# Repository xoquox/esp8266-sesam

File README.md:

# esp8266-sesam

Universal Wifi door opener. 

A project by [schinken](https://github.com/schinken "schinkens Github") and [xoquox](https://github.com/xoquox "xoquoxs Github")

# Hardware

Our hardware works with a ESP-08 or ESP-12e modul. It uses nice little DIL relays, becaus we can direct control them with TTL-signals. What I think is very nice for a relay. 

# Webinterface
  TODO

# REST-API
  TODO

# License
  TODOh

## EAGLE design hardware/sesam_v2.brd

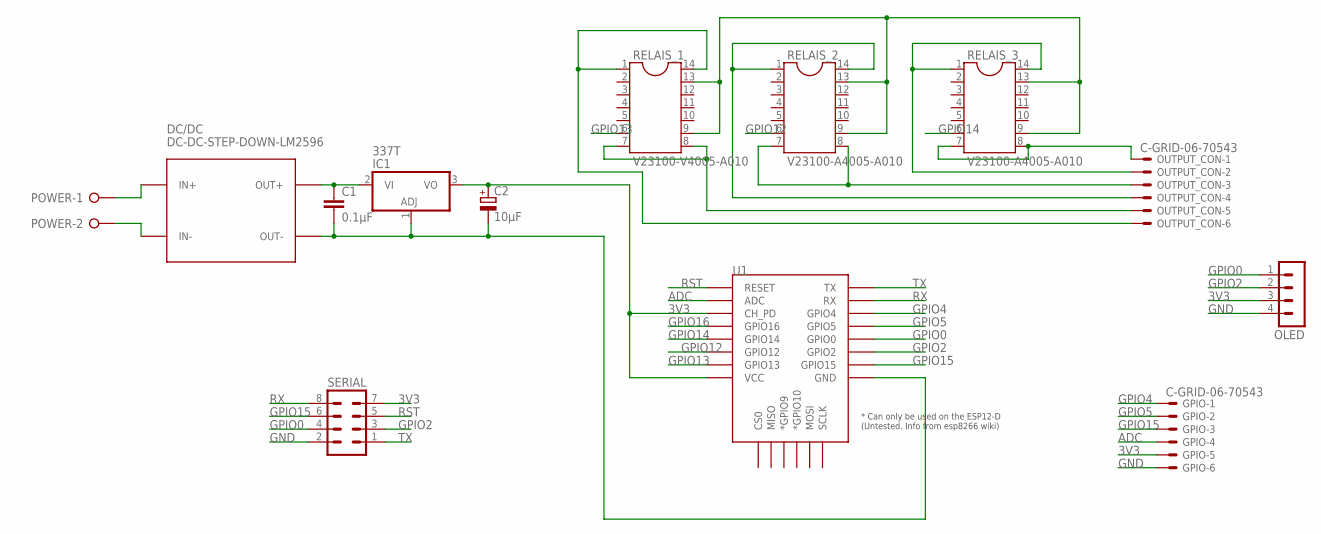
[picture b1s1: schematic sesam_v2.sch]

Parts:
C1: 0.1µF; C0805
C2: 10µF; E2-5
DC/DC: DC-DC-STEP-DOWN-LM2596
GPIO: C-GRID-06-70543; 70543-06
IC1: 337T; TO220H
OLED: MA04-1
OUTPUT_CON: C-GRID-06-70543; 70543-06
POWER: W237-02P; W237-132
RELAIS_1: V23100-V4005-A010; SOCKET-14
RELAIS_2, RELAIS_3: V23100-A4005-A010; SOCKET-14
SERIAL: MA04-2
U1: ESP12ESMD; ESP12E-SMD

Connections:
3V3: C2.+, GPIO.5, IC1.3 (VO), OLED.3, SERIAL.7, U1.CH_PD, U1.VCC
ADC: GPIO.4, U1.ADC
GND: C1.2, C2.-, DC/DC.IN-, DC/DC.OUT-, GPIO.6, IC1.1 (ADJ), OLED.4, POWER.2, RELAIS_1.9, RELAIS_1.13, RELAIS_2.9, RELAIS_2.13, RELAIS_3.9, RELAIS_3.13, SERIAL.2, U1.GND
GPIO0: OLED.1, SERIAL.4, U1.GPIO0
GPIO2: OLED.2, SERIAL.3, U1.GPIO2
GPIO4: GPIO.1, U1.GPIO4
GPIO5: GPIO.2, U1.GPIO5
GPIO12: RELAIS_2.6, U1.GPIO12
GPIO13: RELAIS_1.6, U1.GPIO13
GPIO14: RELAIS_3.6, U1.GPIO14
GPIO15: GPIO.3, SERIAL.6, U1.GPIO15
GPIO16: U1.GPIO16
unnamed 14: OUTPUT_CON.2, RELAIS_3.1, RELAIS_3.14; also elsewhere on the board
unnamed: DC/DC.IN+, POWER.1
unnamed 16: OUTPUT_CON.1, RELAIS_3.7, RELAIS_3.8; also elsewhere on the board
unnamed 17: OUTPUT_CON.4, RELAIS_2.1, RELAIS_2.14; also elsewhere on the board
unnamed 18: OUTPUT_CON.3, RELAIS_2.7, RELAIS_2.8; also elsewhere on the board
unnamed 19: OUTPUT_CON.6, RELAIS_1.1, RELAIS_1.14; also elsewhere on the board
unnamed 20: OUTPUT_CON.5, RELAIS_1.7, RELAIS_1.8; also elsewhere on the board
POWER: C1.1, DC/DC.OUT+, IC1.2 (VI)
RST: SERIAL.5, U1.RESET
RX: SERIAL.8, U1.RXD0 (RX)
TX: SERIAL.1, U1.TXD0 (TX)

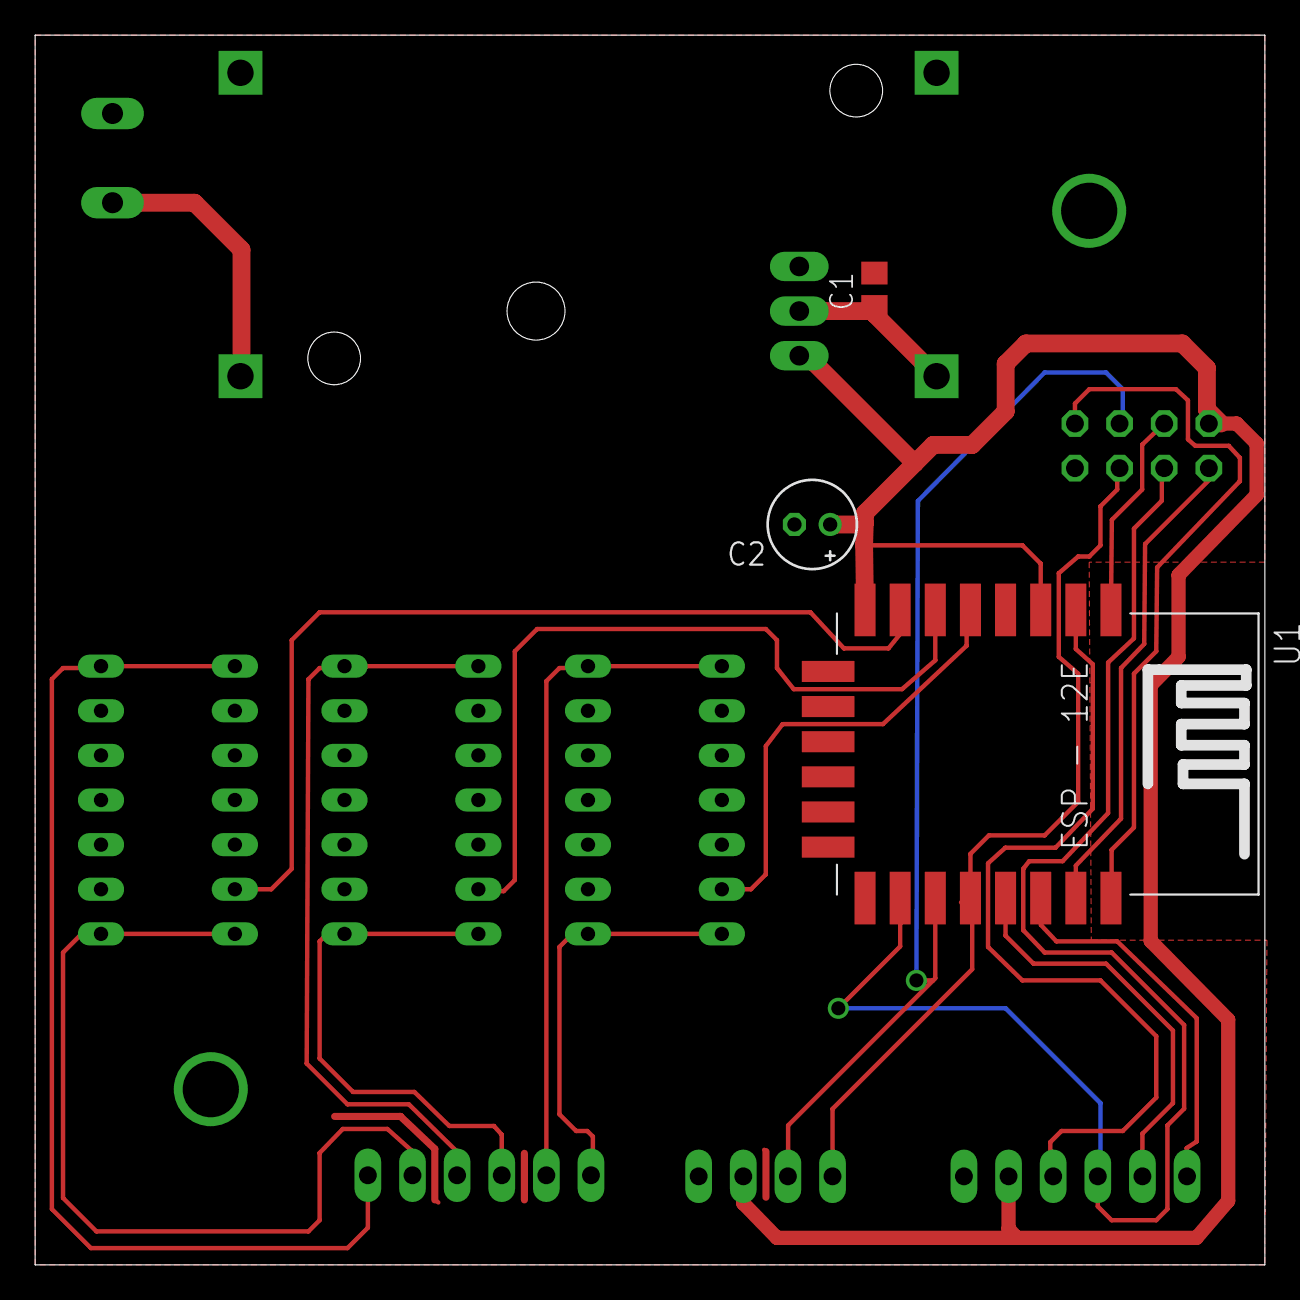
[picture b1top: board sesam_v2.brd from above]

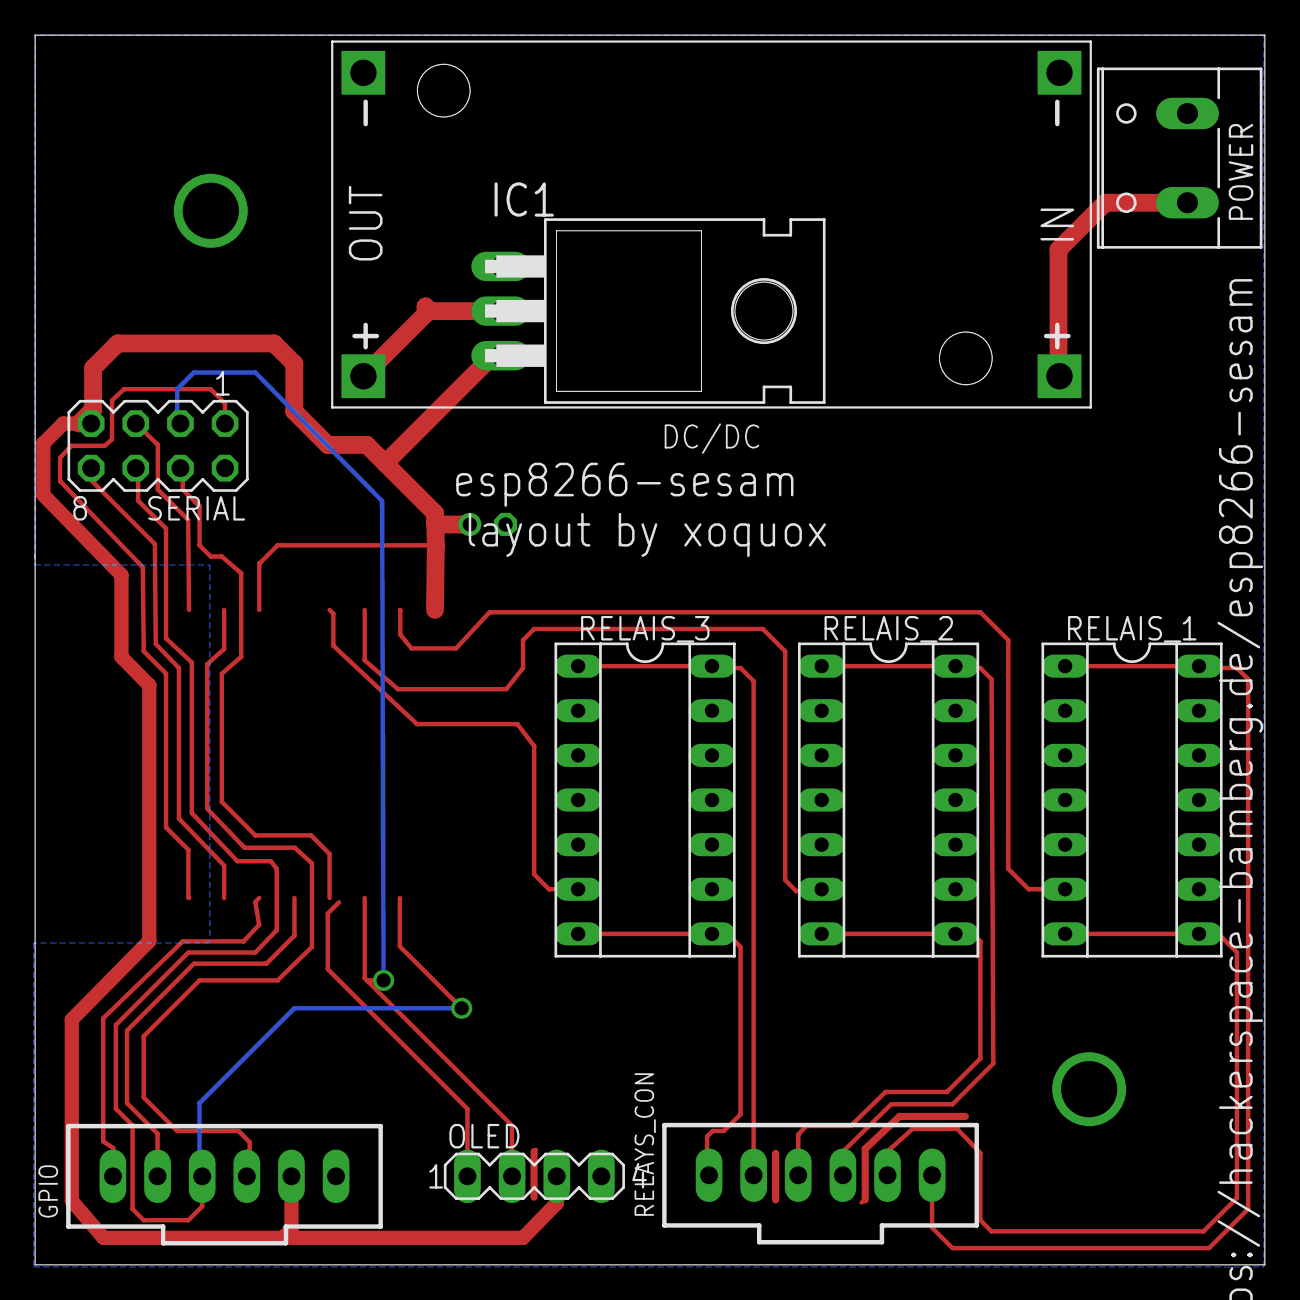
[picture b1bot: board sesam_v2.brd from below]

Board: 2 copper layers, 70.0 x 70.0 mm, 13 parts (10 on the bottom side), 22 nets.

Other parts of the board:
RELAYS_CON: C-GRID-06-70543; 70543-06

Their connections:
unnamed 14: RELAYS_CON.2; also elsewhere on the board
unnamed 16: RELAYS_CON.1; also elsewhere on the board
unnamed 17: RELAYS_CON.4; also elsewhere on the board
unnamed 18: RELAYS_CON.3; also elsewhere on the board
unnamed 19: RELAYS_CON.6; also elsewhere on the board
unnamed 20: RELAYS_CON.5; also elsewhere on the board

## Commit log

2016-02-12 Set pinmode; Add caching directives
2016-02-12 Add random parameter to prevent browser caching
2016-02-12 Prevent caching also on /
2016-02-12 Introduce open.html to avoid caching
2016-05-16 hardware files added
2016-05-18 new layout by hallojoh
2016-05-18 Create a Readme.
2016-05-18 new layout, all non smd components mirrored
2016-05-18 Bottom added
2016-05-18 layout images added
2016-05-19 minor changes
2016-05-19 little changes
2016-05-19 new nice layout
2016-05-19 ready for first board
2016-05-19 some little changes, .gitignore for usless eagle files added and also some of this files removed from tree
2016-05-20 removed eagle backup files from tree
2016-05-20 minor tweeks
2016-05-21 rename of source file
2016-05-21 nice new layout and board, better power supply added
2016-05-21 fixed power regulator
2016-05-22 some layout tweeks
2016-05-22 fixed GND connections
2016-05-22 Make button/relais configurable
2016-05-22 Fix whitespaces and indention
2016-05-22 Optimize whitespaces for faster loading
2016-05-22 Fix button width
2016-05-22 More margin between buttons

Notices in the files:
parts and their libraries:
diy-modules: Released under the Creative Commons Attribution 4.0 International License: http://creativecommons.org/licenses/by/4.0
